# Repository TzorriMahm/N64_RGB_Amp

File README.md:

# N64 RGB Amp
**A modding board to achieve RGB video on some early NTSC models by using TI's THS7374 video amplifier.**<br>

<br><br>
**⁓ Designed with ♥ in Germany ⁓**<br><br>

# Where to get the PCB?
You can order the PCB directly from [OSHPark](https://oshpark.com/shared_projects/cdlxvTEA).
Of course, feel free to use the gerber files with any manufacturer of your choice.<br>
Use 0.8mm board thickness to ensure an easy and clean installation.

# Before you start
**This modification only works with NUS-CPU-01/02/03/04 main board revisions!**<br>
Also, verify that your main board has a 'VDC-NUS'/'VDC-NUS A' chip (U4).<br>
If that's not the case - **stop here!** Your console is not compatible with this modding board!

# Install instructions
## Bottom metal shielding
Use a pair of pliers to bend away the tab which is located at the MultiOut area.<br>
This avoids the shielding from hitting the modding board later.

<br>

## Preparing the N64 main board
- remove R1, R14, R15, R16, C22

## Installing the modding board
- isolate the bottom side of the modding board to avoid any shorts
- solder the modding board onto the pins of the MultiOut
- solder a wire from the via next to R8 (N64 main board) to pad 'R' (modding board)
- solder a wire from the via next to R9 (N64 main board) to pad 'G' (modding board)
- solder a wire from the via next to R10 (N64 main board) to pad 'B' (modding board)
- solder a wire from the via next to R16 (N64 main board) to pad 'CS' (modding board)<br>

## Install diagram

# Troubleshooting
Double-check continuity between connections:
- 'R' (modding board) ⇄ VDC-NUS(A) pin 17 (N64 main board)
- 'G' (modding board) ⇄ VDC-NUS(A) pin 19 (N64 main board)
- 'B' (modding board) ⇄ VDC-NUS(A) pin 21 (N64 main board)
- 'CS' (modding board) ⇄ VDC-NUS(A) pin 14 (N64 main board)

**Check for shorts to VDC-NUS(A)!** The vias you solder to are located directly beneath that IC.<br>
It's ridiculously-simple to short something when the exposed conductors are a little bit too long!

# Miscellaneous
#### Jumper 'J:LPF'
The THS7374 has a low pass filter on each of the four channels which can be turned on by shorting jumper 'J:LPF' on the modding board. This is mostly needed if you wire the console directly to a flat-screen TV. There's no need for the low pass filter on analogue devices.<br>
If you use an OSSC or a Framemeister, it's better to use their filter options.

#### RGB cable
You will need a RGB cable with 220µF electrolytic capacitors on each of the 'R', 'G' & 'B' lines. The positive end is facing towards the console.<br>
This modding board is designed to output TTL level C-Sync directly at the MultiOut of the console.<br>
With that in mind, make sure you're using a suitable cable with a 470Ω resistor on the sync line to use it with most consumer products (like TV's, OSSC, Framemeister)!

# Disclaimer
I am not responsible for any damage to you, your devices or anything else!<br>
If you do the modification, you do it at your own risk and responsibility!

# Acknowledgement
Most of the credits should go to [borti4938](https://github.com/borti4938). He has made the actual (slightly different) circuit and inspired me to design this board. Thanks man! Thanks Bob, for your awesome and informative website [RetroRGB](http://retrorgb.com)!<br>
And of course, thanks to the whole retro gaming community for keeping the spirit alive!

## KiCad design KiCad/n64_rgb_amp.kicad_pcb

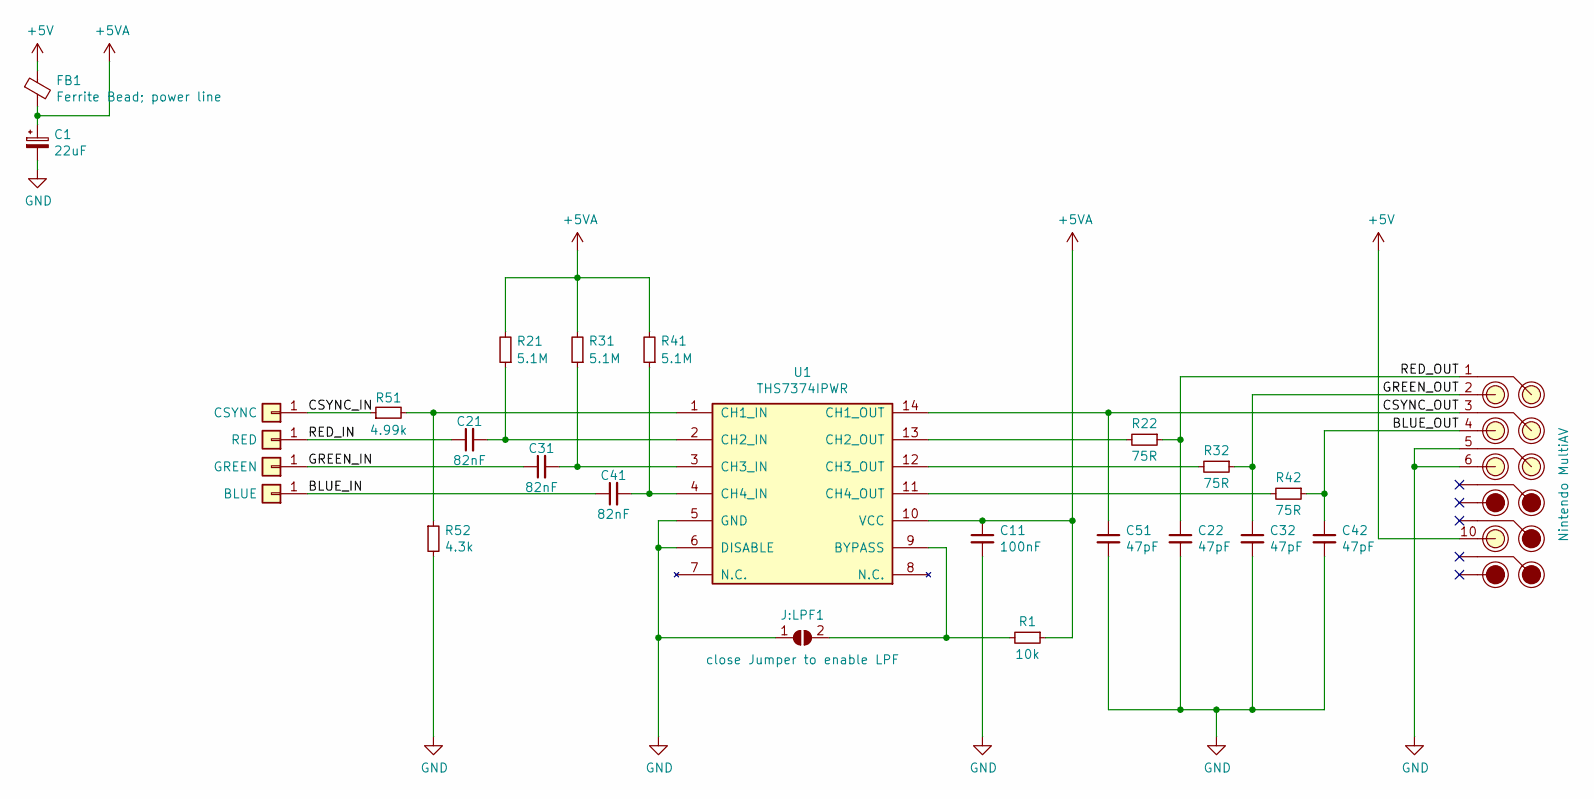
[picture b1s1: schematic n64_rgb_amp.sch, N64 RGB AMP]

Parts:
C1: 22uF; C_SMD0805
C11: 100nF; C_SMD0603
C21, C31, C41: 82nF; C_SMD0603
C22, C32, C42, C51: 47pF; C_SMD0603
FB1: Ferrite Bead; power line; FB_SMD0603
INPUT_1: RED; SolderPad_customizable
INPUT_2: GREEN; SolderPad_customizable
INPUT_3: BLUE; SolderPad_customizable
INPUT_4: CSYNC; SolderPad_customizable
J:LPF1: close Jumper to enable LPF; SolderJumper_2x0.75x1mm
MultiAV1: Nintendo MultiAV; NintendoMultiAV_FB-gap
R1: 10k; R_SMD0603
R21, R31, R41: 5.1M; R_SMD0603
R22, R32, R42: 75R; R_SMD0603
R51: 4.99k; R_SMD0603
R52: 4.3k; R_SMD0603
U1: THS7374IPWR; TSSOP-14

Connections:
+5V: FB1.1, MultiAV1.10
+5VA: C1.1, C11.1, FB1.2, R1.1, R21.2, R31.2, R41.2, U1.10 (VCC)
/BLUE_IN: C41.1, INPUT_3.1
/BLUE_OUT: C42.1, MultiAV1.4, R42.1
/CSYNC_IN: INPUT_4.1, R51.1
/CSYNC_OUT: C51.1, MultiAV1.3, U1.14 (CH1_OUT)
/GREEN_IN: C31.1, INPUT_2.1
/GREEN_OUT: C32.1, MultiAV1.2, R32.1
/RED_IN: C21.1, INPUT_1.1
/RED_OUT: C22.1, MultiAV1.1, R22.1
GND: C1.2, C11.2, C22.2, C32.2, C42.2, C51.2, J:LPF1.1 (A), MultiAV1.5, MultiAV1.6, R52.2, U1.5 (GND), U1.6 (DISABLE)
unnamed: C21.2, R21.1, U1.2 (CH2_IN)
unnamed: C31.2, R31.1, U1.3 (CH3_IN)
unnamed: C41.2, R41.1, U1.4 (CH4_IN)
unnamed: J:LPF1.2 (B), R1.2, U1.9 (BYPASS)
unnamed: R22.2, U1.13 (CH2_OUT)
unnamed: R32.2, U1.12 (CH3_OUT)
unnamed: R42.2, U1.11 (CH4_OUT)
unnamed: R51.2, R52.1, U1.1 (CH1_IN)

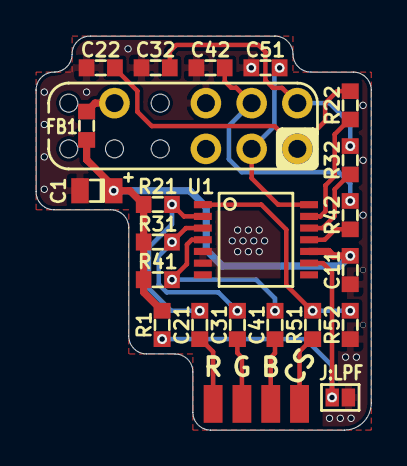
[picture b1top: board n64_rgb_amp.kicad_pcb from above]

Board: 2 copper layers, 18.6 x 21.9 mm, 27 parts (1 on the bottom side), 19 nets.

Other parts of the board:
***: TM_logo-silk

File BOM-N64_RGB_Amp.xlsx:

N64 RGB Amp - Bill of Materials
Designator | Mfr. No | Quantity | Description | Package | Value | Mouser
U1 | THS7374IPWR | 1 | 4-Ch. SD Video Amp | TSSOP-14 |  | https://www.mouser.de/ProductDetail/Texas-Instruments/THS737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
C1 | 08053D226MAT2A | 1 | Ceramic capacitor; X5R; 25V | SMD0805 | 22µF / 20% | https://www.mouser.de/ProductDetail/AVX/08053D226MAT2A?qs=bx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
C11 | 06035C104KAT2A | 1 | Ceramic capacitor; X7R; 50V | SMD0603 | 100nF / 10% | https://www.mouser.de/ProductDetail/AVX/06035C104KAT2A?qs=wO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
C21, C31, C31 | 0603YC823KAT2A | 3 | Ceramic capacitor; X7R; 16V | SMD0603 | 82nF / 10% | https://www.mouser.de/ProductDetail/AVX/0603YC823KAT2A?qs=Gc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
C22, C32, C42, C51 | 0603YC470KAT2A | 4 | Ceramic capacitor; X7R, 16V | SMD0603 | 47pF / 10% | https://www.mouser.de/ProductDetail/AVX/0603YC470KAT2A?qs=EU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
FB1 | MPZ1608S221ATA00 | 1 | Ferrite bead; power line | SMD0603 |  | https://www.mouser.de/ProductDetail/TDK/MPZ1608S221ATA00?qs=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
R1 | RC0603FR-0710KL | 1 | Resistor; 1/10W | SMD0603 | 10kΩ / 1% | https://www.mouser.de/ProductDetail/Yageo/RC0603FR-0710KL?qs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
R21, R31, R41 | RC0603FR-075M1L | 3 | Resistor; 1/10W | SMD0603 | 5.1MΩ / 1% | https://www.mouser.de/ProductDetail/Yageo/RC0603FR-075M1L?qs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
R22, R32, R42 | RC0603FR-0775RL | 3 | Resistor; 1/10W | SMD0603 | 75Ω / 1% | https://www.mouser.de/ProductDetail/Yageo/RC0603FR-0775RL?qs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
R51 | RC0603FR-074K7L | 1 | Resistor; 1/10W | SMD0603 | 4.7kΩ / 1% | https://www.mouser.de/ProductDetail/Yageo/RC0603FR-074K7L?qs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
R52 | RC0603FR-0710K7L | 1 | Resistor; 1/10W | SMD0603 | 10.7kΩ / 1% | https://www.mouser.de/ProductDetail/Yageo/RC0603FR-0710K7L?q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
Mouser Basket: | https://www.mouser.de/ProjectManager/ProjectDetail.aspx?Acce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

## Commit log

2020-12-17 Add KiCad design files; update to v3.2
    - add KiCad design files
    - update to v3.2; minor changes - nothing special
2020-12-17 Add KiCad design files; update to v1.1
    - add KiCad design files
    - update to v1.1; minor changes - nothing special
2020-12-17 Revert "Add KiCad design files; update to v3.2"
    This reverts commit 25f73cbb464701b12caae3678c85ef64555b3520.
2020-12-17 Add KiCad files for v1.1
    - project file
    - schematics
    - design
    - libraries
    - footprints
2020-12-17 Replace gerber files to match v1.1
2020-12-17 Update README.md
    - changes the link to OSHPark
2022-09-05 Fixed typo in BOM. Thanks, @hitmanmcc!
